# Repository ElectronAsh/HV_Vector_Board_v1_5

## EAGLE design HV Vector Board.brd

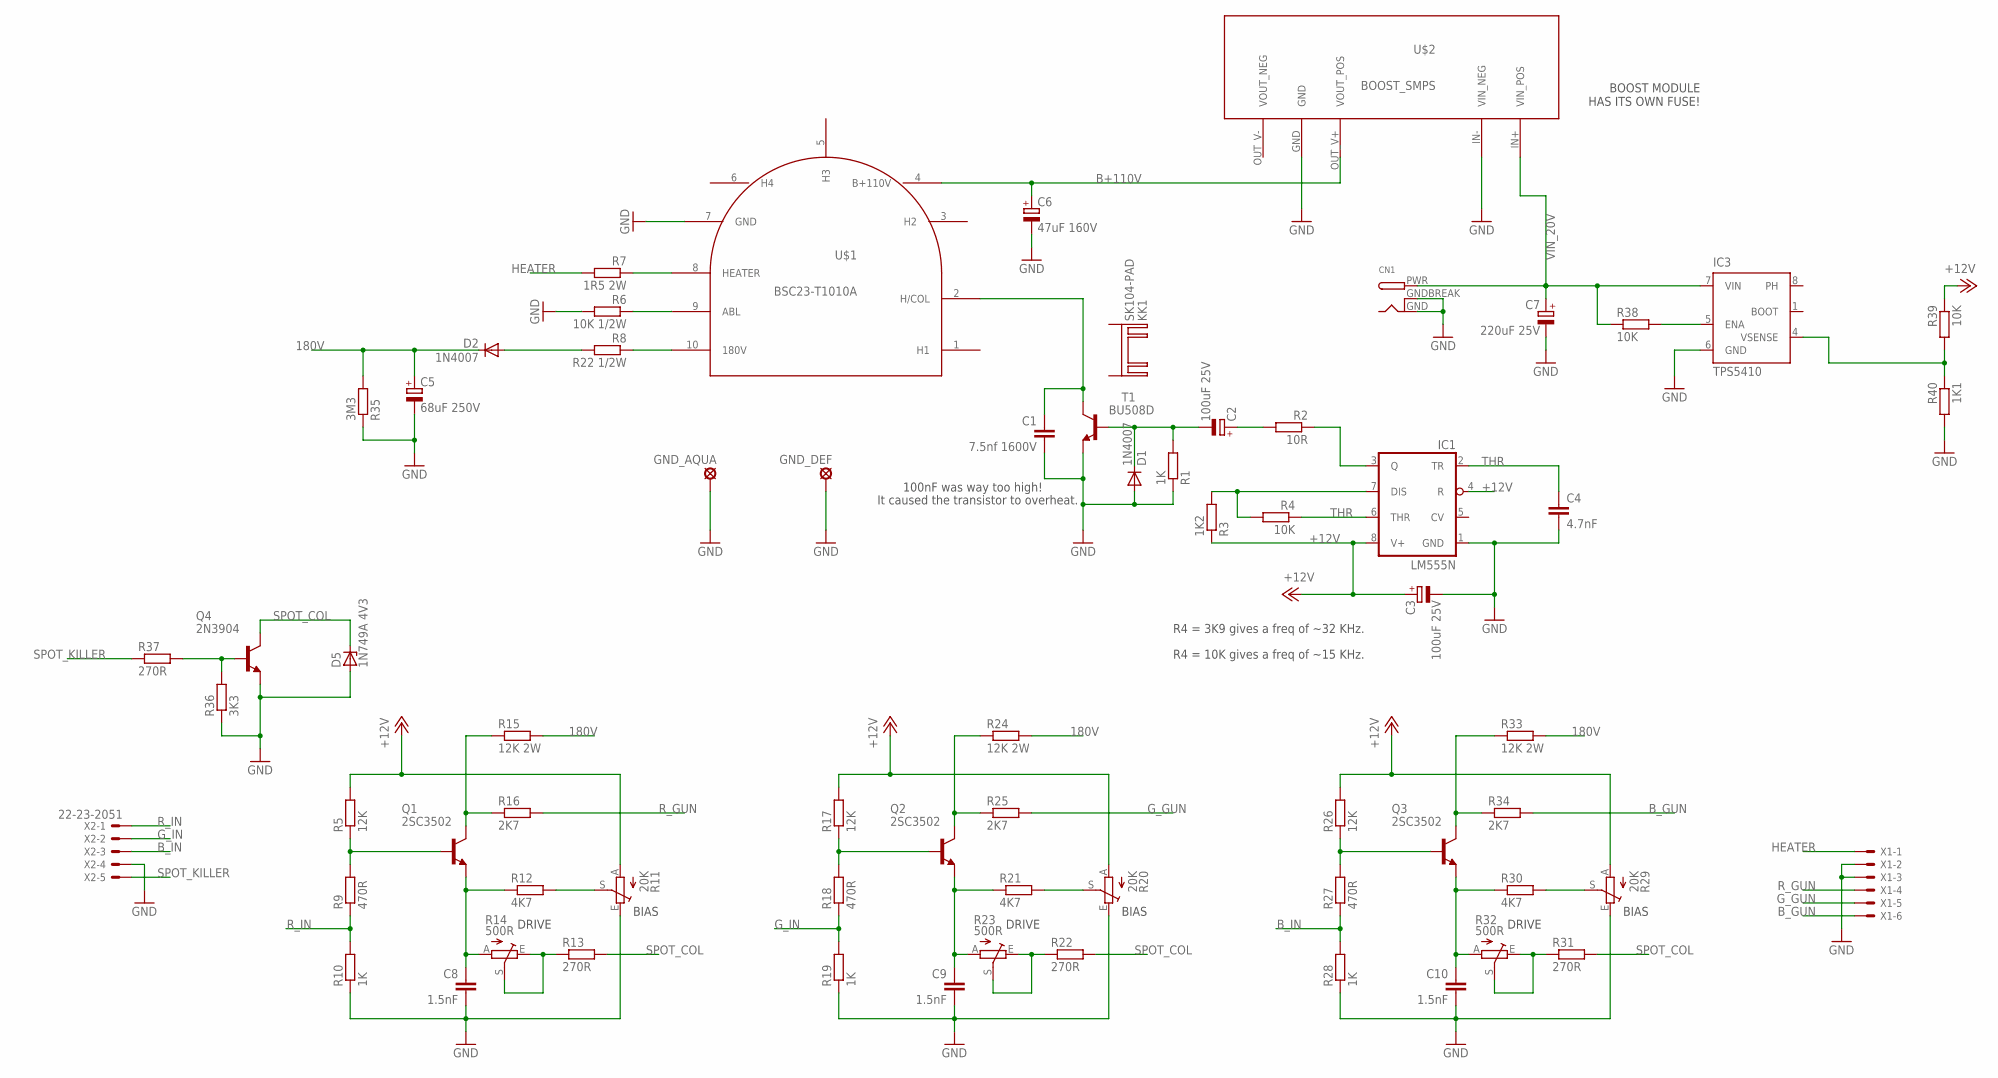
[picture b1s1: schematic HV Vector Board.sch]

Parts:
C1: 7.5nf 1600V; C075-052X106
C2, C3: 100uF 25V; E2-5
C4: 4.7nF; C025-025X050
C5: 68uF 250V; E5-8,5
C6: 47uF 160V; E3,5-8
C7: 220uF 25V; E5-8,5
C8, C9, C10: 1.5nF; C025-025X050
CN1: DCBARRELPTH; DCJACK_2MM_PTH
D1, D2: 1N4007; DO41-10
D5: 1N749A 4V3; ZDIO-7.5
GND_AQUA: SE14
GND_DEF: SE14
IC1: LM555N; DIL08
IC3: TPS5410; D_R-PDSO-G08
KK1: SK104-PAD
Q1, Q2, Q3: 2SC3502; TO126
Q4: 2N3904; TO92
R1: 1K; 0207/10
R2: 10R; 0204/7
R3: 1K2; 0204/7
R4, R38, R39: 10K; 0204/7
R5, R17, R26: 12K; 0204/7
R6: 10K 1/2W; 0207/10
R7: 1R5 2W; 0309/12
R8: R22 1/2W; 0204/7
R9, R18, R27: 470R; 0204/7
R10, R19, R28: 1K; 0204/7
R11, R20, R29: 20K; RS3
R12, R21, R30: 4K7; 0204/7
R13, R22, R31, R37: 270R; 0204/7
R14, R23, R32: 500R; RS3
R15, R24, R33: 12K 2W; 0309/12
R16, R25, R34: 2K7; 0204/7
R35: 3M3; 0204/7
R36: 3K3; 0204/7
R40: 1K1; 0204/7
T1: BU508D; TO218V
U$1: BSC23-T1010A; BSC25_FLYBACK
U$2: BOOST_SMPS; BOOST_PSU
X1: 22-23-2061
X2: 22-23-2051

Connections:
180V: C5.+, D2.C, R15.2, R24.2, R33.2, R35.2
+12V: C3.+, IC1.4 (R), IC1.8 (V+), R3.1, R5.2, R11.A, R17.2, R20.A, R26.2, R29.A, R39.1
ABL: R6.1, U$1.9 (ABL)
B+110V: C6.+, U$1.4 (B+110V), U$2.OUT_V+ (VOUT_POS)
B_DRV_WIPE: R31.1, R32.E, R32.S
B_GUN: R34.2, X1.6
B_IN: R27.1, R28.2, X2.3
GND: C1.2, C3.-, C4.2, C5.-, C6.-, C7.-, C8.2, C9.2, C10.2, CN1.GND, CN1.GNDBREAK, D1.A, D5.A, GND_AQUA.MP, GND_DEF.MP, IC1.1 (GND), IC3.6 (GND), Q4.3 (E), R1.1, R6.2, R10.1, R11.E, R19.1, R20.E, R28.1, R29.E, R35.1, R36.1, R40.2, T1.3 (E), U$1.7 (GND), U$2.GND, U$2.IN- (VIN_NEG), X1.2, X1.3, X2.4
G_DRV_WIPE: R22.1, R23.E, R23.S
G_GUN: R25.2, X1.5
G_IN: R18.1, R19.2, X2.2
HEATER: R7.2, X1.1
unnamed: C1.1, T1.2 (C), U$1.2 (H/COL)
unnamed: R7.1, U$1.8 (HEATER)
unnamed: C2.-, D1.C, R1.2, T1.1 (B)
unnamed: C2.+, R2.2
unnamed: IC1.3 (Q), R2.1
unnamed: Q2.3 (B), R17.1, R18.2
unnamed: R8.1, U$1.10 (180V)
unnamed: D2.A, R8.2
unnamed: Q4.2 (B), R36.2, R37.2
unnamed: IC1.7 (DIS), R3.2, R4.2
unnamed: C9.1, Q2.1 (E), R21.1, R23.A
unnamed: Q1.3 (B), R5.1, R9.2
unnamed: C8.1, Q1.1 (E), R12.1, R14.A
unnamed: R11.S, R12.2
unnamed: IC3.4 (VSENSE), R39.2, R40.1
unnamed: IC3.5 (ENA), R38.2
unnamed: Q1.2 (C), R15.1, R16.1
unnamed: R20.S, R21.2
unnamed: Q2.2 (C), R24.1, R25.1
unnamed: Q3.3 (B), R26.1, R27.2
unnamed: C10.1, Q3.1 (E), R30.1, R32.A
unnamed: R29.S, R30.2
unnamed: Q3.2 (C), R33.1, R34.1
R_DRV_WIPE: R13.1, R14.E, R14.S
R_GUN: R16.2, X1.4
R_IN: R9.1, R10.2, X2.1
SPOT_COL: D5.C, Q4.1 (C), R13.2, R22.2, R31.2
SPOT_KILLER: R37.1, X2.5
THR: C4.1, IC1.2 (TR), IC1.6 (THR), R4.1
VIN_20V: C7.+, CN1.PWR, IC3.7 (VIN), R38.1, U$2.IN+ (VIN_POS)

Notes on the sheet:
BIAS
DRIVE
BOOST MODULE HAS ITS OWN FUSE!
100nF was way too high!
It caused the transistor to overheat.
R4 = 3K9 gives a freq of ~32 KHz.
R4 = 10K gives a freq of ~15 KHz.

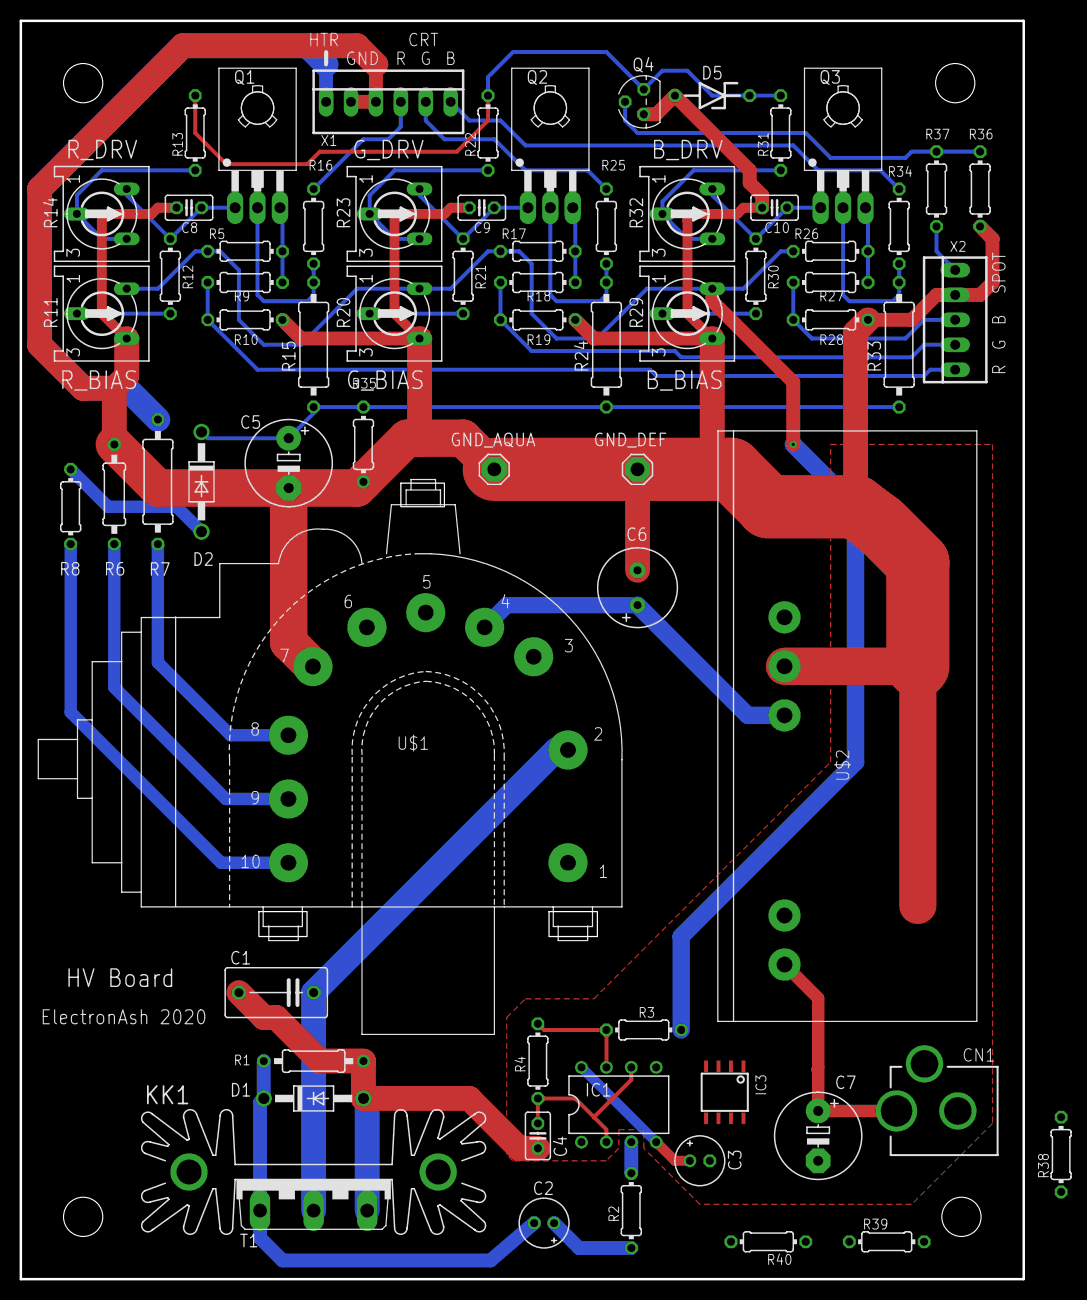
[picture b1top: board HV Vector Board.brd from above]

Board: 2 copper layers, 102.2 x 128.3 mm, 68 parts (0 on the bottom side), 42 nets.
